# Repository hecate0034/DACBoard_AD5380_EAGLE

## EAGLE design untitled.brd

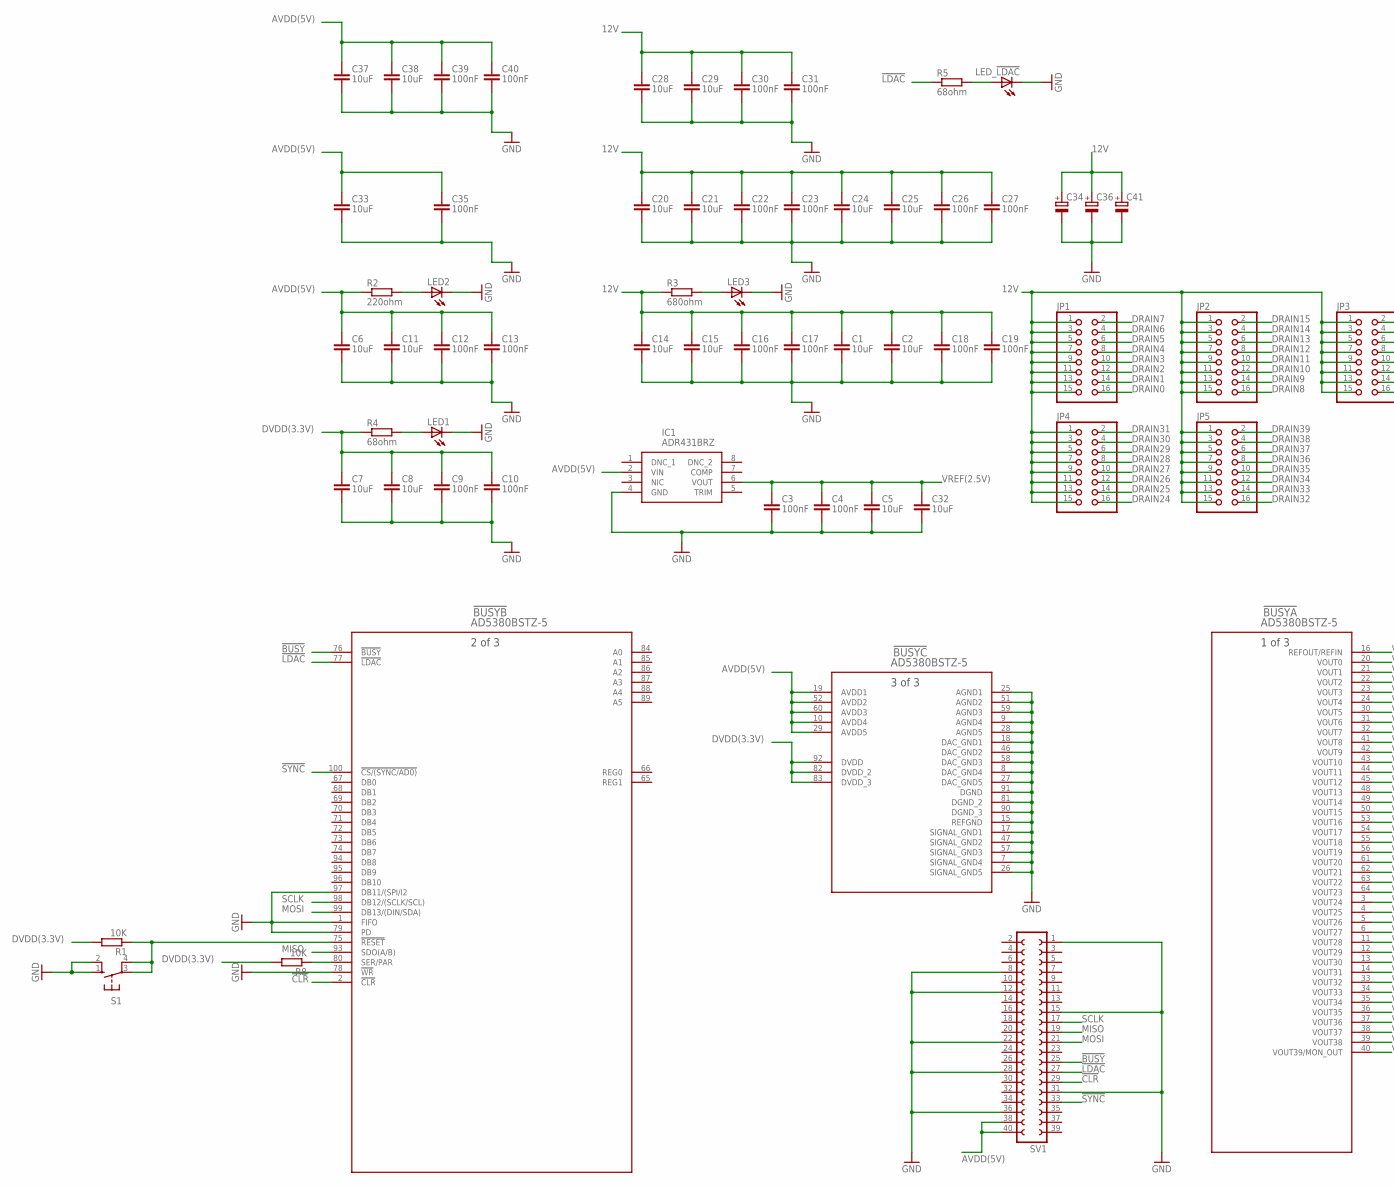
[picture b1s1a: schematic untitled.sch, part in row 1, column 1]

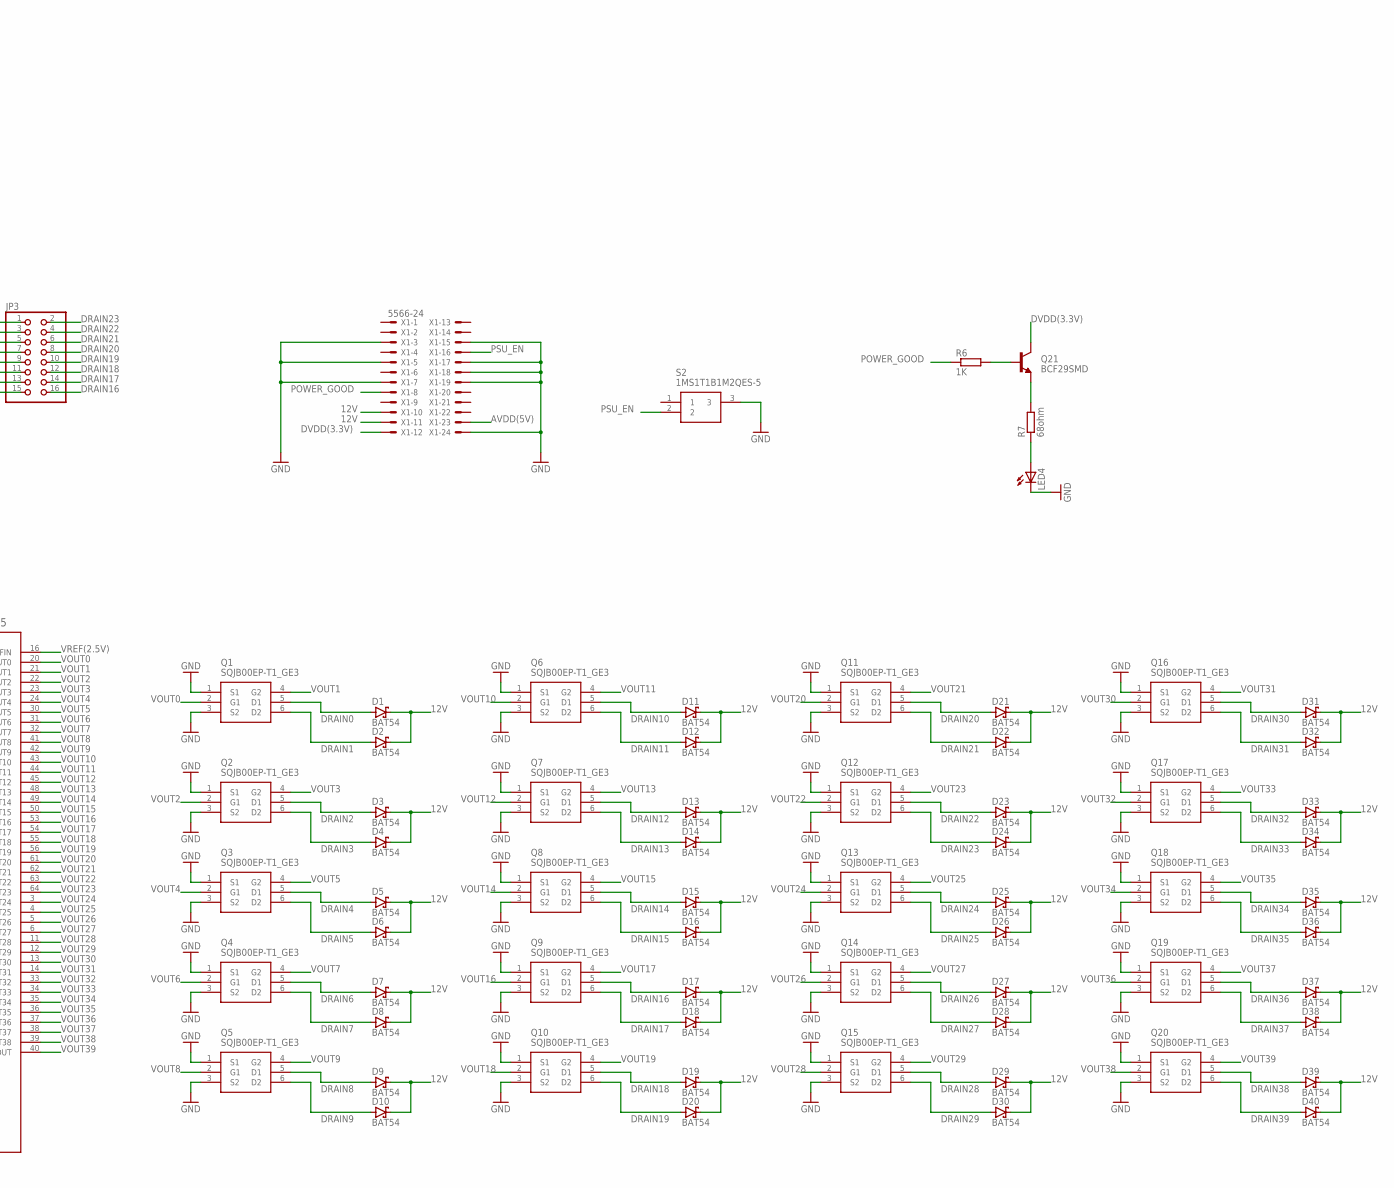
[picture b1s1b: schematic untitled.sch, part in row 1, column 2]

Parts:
!BUSY: AD5380BSTZ-5; ST_100_1
C1, C2, C5, C6, C7, C8, C11, C14, C15, C20, C21, C24, C25, C28, C29, C32, C33, C37, C38: 10uF; C1206
C3, C4, C9, C10, C12, C13, C16, C17, C18, C19, C22, C23, C26, C27, C30, C31, C35, C39, C40: 100nF; C0603
C34, C36: CPOL-EUE2-4; E2-4
C41: CPOL-EUE3.5-10; E3,5-10
D1, D2, D3, D4, D5, D6, D7, D8, D9, D10, D11, D12, D13, D14, D15, D16, D17, D18, D19, D20, D21, D22, D23, D24, D25, D26, D27, D28, D29, D30, D31, D32, D33, D34, D35, D36, D37, D38, D39, D40: BAT54; SOT23
IC1: ADR431BRZ; SOIC127P600X175-8N
JP1, JP2, JP3, JP4, JP5: PINHD-2X8; 2X08
LED1, LED2, LED3, LED4: LEDCHIPLED_0603; CHIPLED_0603
LED_!LDAC: LEDCHIPLED_0603; CHIPLED_0603
Q1, Q2, Q3, Q4, Q5, Q6, Q7, Q8, Q9, Q10, Q11, Q12, Q13, Q14, Q15, Q16, Q17, Q18, Q19, Q20: SQJB00EP-T1_GE3; SQJ968EPT1GE3
Q21: BCF29SMD; SOT23-BEC
R1, R8: 10K; R0603
R2: 220ohm; R0805
R3: 680ohm; R0805
R4, R5, R7: 68ohm; R0805
R6: 1K; R0805
S1: 10-XX; B3F-10XX
S2: 1MS1T1B1M2QES-5
SV1: FE20-2
X1: 5566-24

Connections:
12V: C1.1, C2.1, C14.1, C15.1, C16.1, C17.1, C18.1, C19.1, C20.1, C21.1, C22.1, C23.1, C24.1, C25.1, C26.1, C27.1, C28.1, C29.1, C30.1, C31.1, C34.+, C36.+, C41.+, D1.3 (C), D2.3 (C), D3.3 (C), D4.3 (C), D5.3 (C), D6.3 (C), D7.3 (C), D8.3 (C), D9.3 (C), D10.3 (C), D11.3 (C), D12.3 (C), D13.3 (C), D14.3 (C), D15.3 (C), D16.3 (C), D17.3 (C), D18.3 (C), D19.3 (C), D20.3 (C), D21.3 (C), D22.3 (C), D23.3 (C), D24.3 (C), D25.3 (C), D26.3 (C), D27.3 (C), D28.3 (C), D29.3 (C), D30.3 (C), D31.3 (C), D32.3 (C), D33.3 (C), D34.3 (C), D35.3 (C), D36.3 (C), D37.3 (C), D38.3 (C), D39.3 (C), D40.3 (C), JP1.1, JP1.3, JP1.5, JP1.7, JP1.9, JP1.11, JP1.13, JP1.15, JP2.1, JP2.3, JP2.5, JP2.7, JP2.9, JP2.11, JP2.13, JP2.15, JP3.1, JP3.3, JP3.5, JP3.7, JP3.9, JP3.11, JP3.13, JP3.15, JP4.1, JP4.3, JP4.5, JP4.7, JP4.9, JP4.11, JP4.13, JP4.15, JP5.1, JP5.3, JP5.5, JP5.7, JP5.9, JP5.11, JP5.13, JP5.15, R3.1, X1.10, X1.11
!BUSY: !BUSY.76 (!BUSY), SV1.25
!CLR: !BUSY.2 (!CLR), SV1.29
!LDAC: !BUSY.77 (!LDAC), R5.1, SV1.27
!RESET: !BUSY.75 (!RESET), R1.1, S1.3, S1.4 (P1)
!SYNC: !BUSY.100 (!CS/(SYNC/AD0)), SV1.33
AVDD(5V): !BUSY.10 (AVDD4), !BUSY.19 (AVDD1), !BUSY.29 (AVDD5), !BUSY.52 (AVDD2), !BUSY.60 (AVDD3), C6.1, C11.1, C12.1, C13.1, C33.1, C35.1, C37.1, C38.1, C39.1, C40.1, IC1.2 (VIN), R2.1, SV1.38, SV1.40, X1.23
DRAIN0: D1.1 (A), JP1.16, Q1.5 (D1)
DRAIN1: D2.1 (A), JP1.14, Q1.6 (D2)
DRAIN2: D3.1 (A), JP1.12, Q2.5 (D1)
DRAIN3: D4.1 (A), JP1.10, Q2.6 (D2)
DRAIN4: D5.1 (A), JP1.8, Q3.5 (D1)
DRAIN5: D6.1 (A), JP1.6, Q3.6 (D2)
DRAIN6: D7.1 (A), JP1.4, Q4.5 (D1)
DRAIN7: D8.1 (A), JP1.2, Q4.6 (D2)
DRAIN8: D9.1 (A), JP2.16, Q5.5 (D1)
DRAIN9: D10.1 (A), JP2.14, Q5.6 (D2)
DRAIN10: D11.1 (A), JP2.12, Q6.5 (D1)
DRAIN11: D12.1 (A), JP2.10, Q6.6 (D2)
DRAIN12: D13.1 (A), JP2.8, Q7.5 (D1)
DRAIN13: D14.1 (A), JP2.6, Q7.6 (D2)
DRAIN14: D15.1 (A), JP2.4, Q8.5 (D1)
DRAIN15: D16.1 (A), JP2.2, Q8.6 (D2)
DRAIN16: D17.1 (A), JP3.16, Q9.5 (D1)
DRAIN17: D18.1 (A), JP3.14, Q9.6 (D2)
DRAIN18: D19.1 (A), JP3.12, Q10.5 (D1)
DRAIN19: D20.1 (A), JP3.10, Q10.6 (D2)
DRAIN20: D21.1 (A), JP3.8, Q11.5 (D1)
DRAIN21: D22.1 (A), JP3.6, Q11.6 (D2)
DRAIN22: D23.1 (A), JP3.4, Q12.5 (D1)
DRAIN23: D24.1 (A), JP3.2, Q12.6 (D2)
DRAIN24: D25.1 (A), JP4.16, Q13.5 (D1)
DRAIN25: D26.1 (A), JP4.14, Q13.6 (D2)
DRAIN26: D27.1 (A), JP4.12, Q14.5 (D1)
DRAIN27: D28.1 (A), JP4.10, Q14.6 (D2)
DRAIN28: D29.1 (A), JP4.8, Q15.5 (D1)
DRAIN29: D30.1 (A), JP4.6, Q15.6 (D2)
DRAIN30: D31.1 (A), JP4.4, Q16.5 (D1)
DRAIN31: D32.1 (A), JP4.2, Q16.6 (D2)
DRAIN32: D33.1 (A), JP5.16, Q17.5 (D1)
DRAIN33: D34.1 (A), JP5.14, Q17.6 (D2)
DRAIN34: D35.1 (A), JP5.12, Q18.5 (D1)
DRAIN35: D36.1 (A), JP5.10, Q18.6 (D2)
DRAIN36: D37.1 (A), JP5.8, Q19.5 (D1)
DRAIN37: D38.1 (A), JP5.6, Q19.6 (D2)
DRAIN38: D39.1 (A), JP5.4, Q20.5 (D1)
DRAIN39: D40.1 (A), JP5.2, Q20.6 (D2)
DVDD(3.3V): !BUSY.82 (DVDD_2), !BUSY.83 (DVDD_3), !BUSY.92 (DVDD), C7.1, C8.1, C9.1, C10.1, Q21.C, R1.2, R4.1, R8.2, X1.12
GND: !BUSY.1 (FIFO), !BUSY.7 (SIGNAL_GND4), !BUSY.8 (DAC_GND4), !BUSY.9 (AGND4), !BUSY.15 (REFGND), !BUSY.17 (SIGNAL_GND1), !BUSY.18 (DAC_GND1), !BUSY.25 (AGND1), !BUSY.26 (SIGNAL_GND5), !BUSY.27 (DAC_GND5), !BUSY.28 (AGND5), !BUSY.46 (DAC_GND2), !BUSY.47 (SIGNAL_GND2), !BUSY.51 (AGND2), !BUSY.57 (SIGNAL_GND3), !BUSY.58 (DAC_GND3), !BUSY.59 (AGND3), !BUSY.78 (!WR), !BUSY.79 (PD), !BUSY.81 (DGND_2), !BUSY.90 (DGND_3), !BUSY.91 (DGND), !BUSY.97 (DB11/(SPI/I2), C1.2, C2.2, C3.2, C4.2, C5.2, C6.2, C7.2, C8.2, C9.2, C10.2, C11.2, C12.2, C13.2, C14.2, C15.2, C16.2, C17.2, C18.2, C19.2, C20.2, C21.2, C22.2, C23.2, C24.2, C25.2, C26.2, C27.2, C28.2, C29.2, C30.2, C31.2, C32.2, C33.2, C34.-, C35.2, C36.-, C37.2, C38.2, C39.2, C40.2, C41.-, IC1.4 (GND), LED1.C, LED2.C, LED3.C, LED4.C, LED_!LDAC.C, Q1.1 (S1), Q1.3 (S2), Q2.1 (S1), Q2.3 (S2), Q3.1 (S1), Q3.3 (S2), Q4.1 (S1), Q4.3 (S2), Q5.1 (S1), Q5.3 (S2), Q6.1 (S1), Q6.3 (S2), Q7.1 (S1), Q7.3 (S2), Q8.1 (S1), Q8.3 (S2), Q9.1 (S1), Q9.3 (S2), Q10.1 (S1), Q10.3 (S2), Q11.1 (S1), Q11.3 (S2), Q12.1 (S1), Q12.3 (S2), Q13.1 (S1), Q13.3 (S2), Q14.1 (S1), Q14.3 (S2), Q15.1 (S1), Q15.3 (S2), Q16.1 (S1), Q16.3 (S2), Q17.1 (S1), Q17.3 (S2), Q18.1 (S1), Q18.3 (S2), Q19.1 (S1), Q19.3 (S2), Q20.1 (S1), Q20.3 (S2), S1.1 (S), S1.2 (S1), S2.3, SV1.1, SV1.8, SV1.12, SV1.15, SV1.22, SV1.28, SV1.31, SV1.36, X1.3, X1.5, X1.7, X1.15, X1.17, X1.18, X1.19, X1.24
MISO: !BUSY.93 (SDO(A/B)), SV1.19
MOSI: !BUSY.99 (DB13/(DIN/SDA)), SV1.21
unnamed: LED2.A, R2.2
unnamed: LED1.A, R4.2
unnamed: LED3.A, R3.2
unnamed: LED_!LDAC.A, R5.2
unnamed: Q21.B, R6.2
unnamed: Q21.E, R7.2
unnamed: LED4.A, R7.1
POWER_GOOD: R6.1, X1.8
PSU_EN: S2.2, X1.16
SCLK: !BUSY.98 (DB12/(SCLK/SCL)), SV1.17
SER/PAR: !BUSY.80 (SER/PAR), R8.1
VOUT0: !BUSY.20 (VOUT0), Q1.2 (G1)
VOUT1: !BUSY.21 (VOUT1), Q1.4 (G2)
VOUT2: !BUSY.22 (VOUT2), Q2.2 (G1)
VOUT3: !BUSY.23 (VOUT3), Q2.4 (G2)
VOUT4: !BUSY.24 (VOUT4), Q3.2 (G1)
VOUT5: !BUSY.30 (VOUT5), Q3.4 (G2)
VOUT6: !BUSY.31 (VOUT6), Q4.2 (G1)
VOUT7: !BUSY.32 (VOUT7), Q4.4 (G2)
VOUT8: !BUSY.41 (VOUT8), Q5.2 (G1)
VOUT9: !BUSY.42 (VOUT9), Q5.4 (G2)
VOUT10: !BUSY.43 (VOUT10), Q6.2 (G1)
VOUT11: !BUSY.44 (VOUT11), Q6.4 (G2)
VOUT12: !BUSY.45 (VOUT12), Q7.2 (G1)
VOUT13: !BUSY.48 (VOUT13), Q7.4 (G2)
VOUT14: !BUSY.49 (VOUT14), Q8.2 (G1)
VOUT15: !BUSY.50 (VOUT15), Q8.4 (G2)
VOUT16: !BUSY.53 (VOUT16), Q9.2 (G1)
VOUT17: !BUSY.54 (VOUT17), Q9.4 (G2)
VOUT18: !BUSY.55 (VOUT18), Q10.2 (G1)
VOUT19: !BUSY.56 (VOUT19), Q10.4 (G2)
VOUT20: !BUSY.61 (VOUT20), Q11.2 (G1)
VOUT21: !BUSY.62 (VOUT21), Q11.4 (G2)
VOUT22: !BUSY.63 (VOUT22), Q12.2 (G1)
VOUT23: !BUSY.64 (VOUT23), Q12.4 (G2)
VOUT24: !BUSY.3 (VOUT24), Q13.2 (G1)
VOUT25: !BUSY.4 (VOUT25), Q13.4 (G2)
VOUT26: !BUSY.5 (VOUT26), Q14.2 (G1)
VOUT27: !BUSY.6 (VOUT27), Q14.4 (G2)
VOUT28: !BUSY.11 (VOUT28), Q15.2 (G1)
VOUT29: !BUSY.12 (VOUT29), Q15.4 (G2)
VOUT30: !BUSY.13 (VOUT30), Q16.2 (G1)
VOUT31: !BUSY.14 (VOUT31), Q16.4 (G2)
VOUT32: !BUSY.33 (VOUT32), Q17.2 (G1)
VOUT33: !BUSY.34 (VOUT33), Q17.4 (G2)
VOUT34: !BUSY.35 (VOUT34), Q18.2 (G1)
VOUT35: !BUSY.36 (VOUT35), Q18.4 (G2)
VOUT36: !BUSY.37 (VOUT36), Q19.2 (G1)
VOUT37: !BUSY.38 (VOUT37), Q19.4 (G2)
VOUT38: !BUSY.39 (VOUT38), Q20.2 (G1)
VOUT39: !BUSY.40 (VOUT39/MON_OUT), Q20.4 (G2)
VREF(2.5V): !BUSY.16 (REFOUT/REFIN), C3.1, C4.1, C5.1, C32.1, IC1.6 (VOUT)

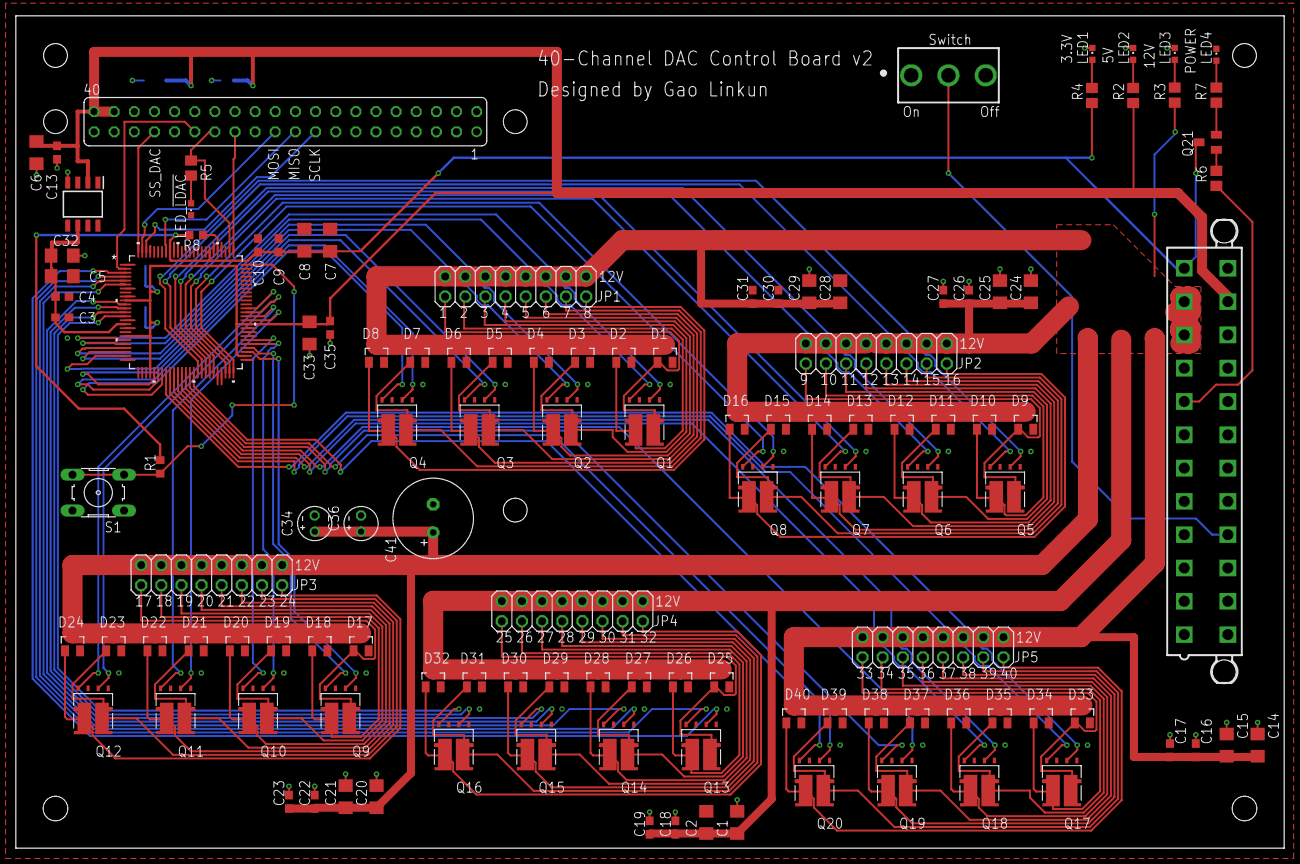
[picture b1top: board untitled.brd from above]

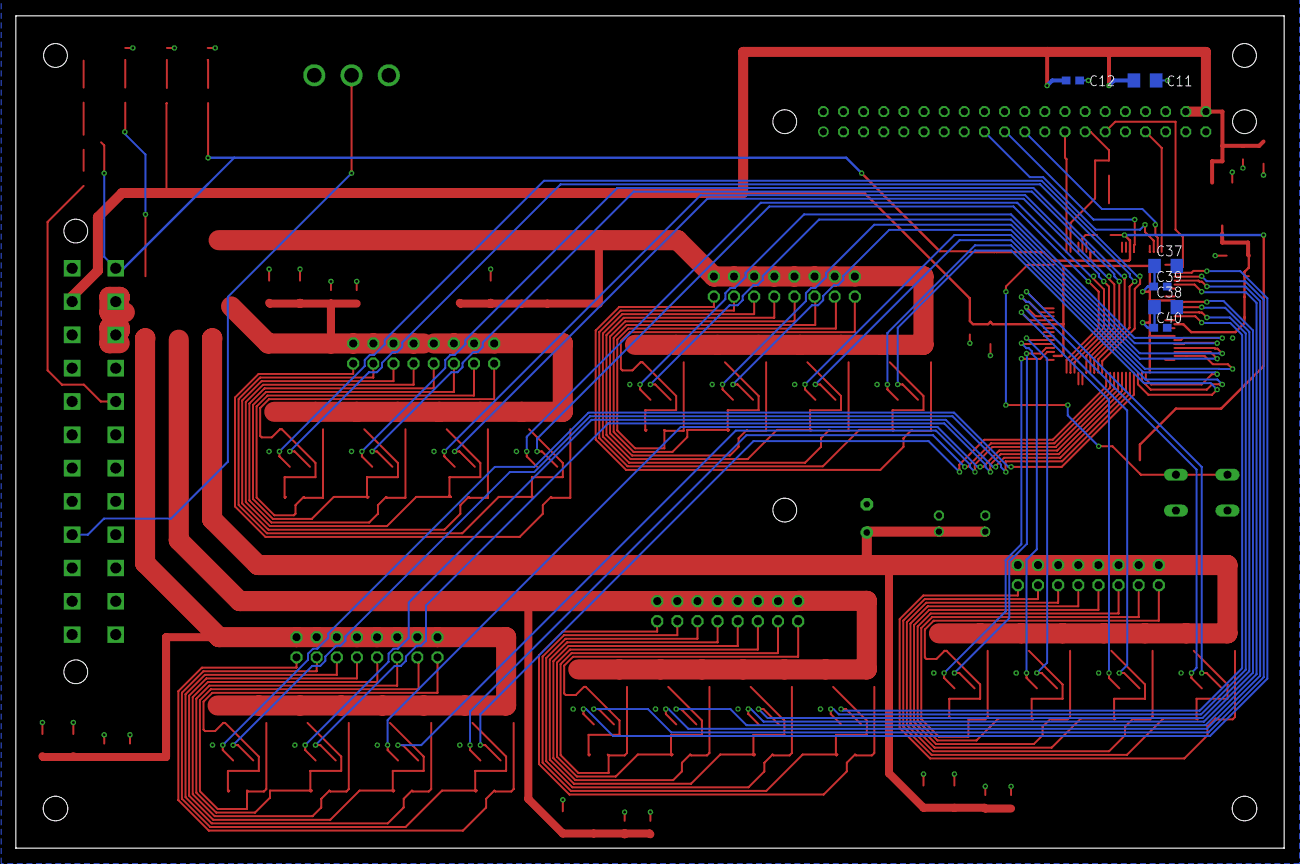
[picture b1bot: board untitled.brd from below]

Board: 4 copper layers, 160.0 x 105.0 mm, 126 parts (6 on the bottom side), 103 nets.

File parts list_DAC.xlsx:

Diode | BAT54 | 40
MOSFET | SQJB00EP-T1_GE3 | 20
Transistor | BCF29SMD(SOT-23) | 1
LED | chipled(0603) | 5
Switch | 1MS1T1B1M2QES-5 | 1
 | B3F-10XX(omron) | 1
Resistor | 68Ω(0805) | 2
 | 220Ω(0805) | 1
 | 680Ω(0805) | 1
 | 1KΩ(0805) | 1
 | 100KΩ(0603) | 1
Capacitor | 470uF | 1
 | 220uF | 1
 | 100uF | 1
 | 10uF(tantalum,C1206) | 19
 | 100nF(ceramic,C0603) | 19
Chip | ADR431BRZ | 1
 | AD5380BSTZ-5 | 1
